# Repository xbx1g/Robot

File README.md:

# 🤖 Robotic Arm with Mecanum Wheels

This project is a **final thesis** for the vocational matura exam.  
It is a mobile robot with **mecanum wheels** and a **robotic arm**, controllable via **Bluetooth** using a custom mobile app.  
The project combines **mechanical engineering, electronics, and programming** – from CAD design and 3D printing, to PCB design, Arduino programming, and mobile app development.

---

## 📌 Features

- Omni-directional movement with **mecanum wheels**  
- **Robotic arm** with multiple degrees of freedom (servo motors)  
- Custom-designed **PCB** for component management  
- **Arduino Mega 2560** as the main controller  
- Control via **Bluetooth module HC-05** and a mobile app (MIT App Inventor)  
- **3D-printed parts** made from PETG filament  
- Powered and tested with **11.1V 3300 mAh LiPo battery**  

---

## 🛠️ Components Used

- Arduino Mega 2560  
- Servo motors (MG996R, SG90)  
- Bipolar stepper motors + **DRV8825 drivers**  
- Bluetooth module **HC-05**  
- Voltage regulator **LM2596**  
- Custom-designed **PCB** (Eagle CAD)  
- 3D-printed parts (Autodesk Inventor + PrusaSlicer, Ender 3 S1 printer)  

---

## 📱 Mobile App

Developed with **MIT App Inventor**.  
Main features:  
- Control of chassis movement (forward/backward/left/right/diagonal)  
- Control of robotic arm (individual joints)  
- Save and execute movement sequences  
- Adjust motor speeds  

---

## 💻 Arduino Code

The Arduino firmware is organized into several modules:  
- **Main program** (initialization, Bluetooth connection)  
- **Chassis movement control**  
- **Robotic arm control**  
- **Movement sequence storage and execution**  
- **Battery voltage monitoring** with LED warning  

---

## 🚀 Getting Started

1. Assemble the robot (chassis, arm, PCB, and wiring).  
2. Upload the Arduino code to **Arduino Mega 2560**.  
3. Install the mobile app (APK) on your smartphone.  
4. Pair with the **HC-05 Bluetooth module**.  
5. Start controlling the robot and test the functionalities.  

---

## 📊 Testing Results

- Battery runtime: ~30 minutes  
- Stepper motor driver temperature after 30 minutes: **45–55 °C**  
- Robot successfully performs omni-directional movements and basic manipulation tasks  

---

## 🔮 Future Improvements

- Add **LCD display** for battery monitoring and step sequence display  
- Support for **Xbox / other Bluetooth controllers**  
- Further PCB optimization and cable management  

---

## 👤 Author

**Marko Koren**  
Mentor: **Peter Zoroja**  
Šolski center Nova Gorica, 2024

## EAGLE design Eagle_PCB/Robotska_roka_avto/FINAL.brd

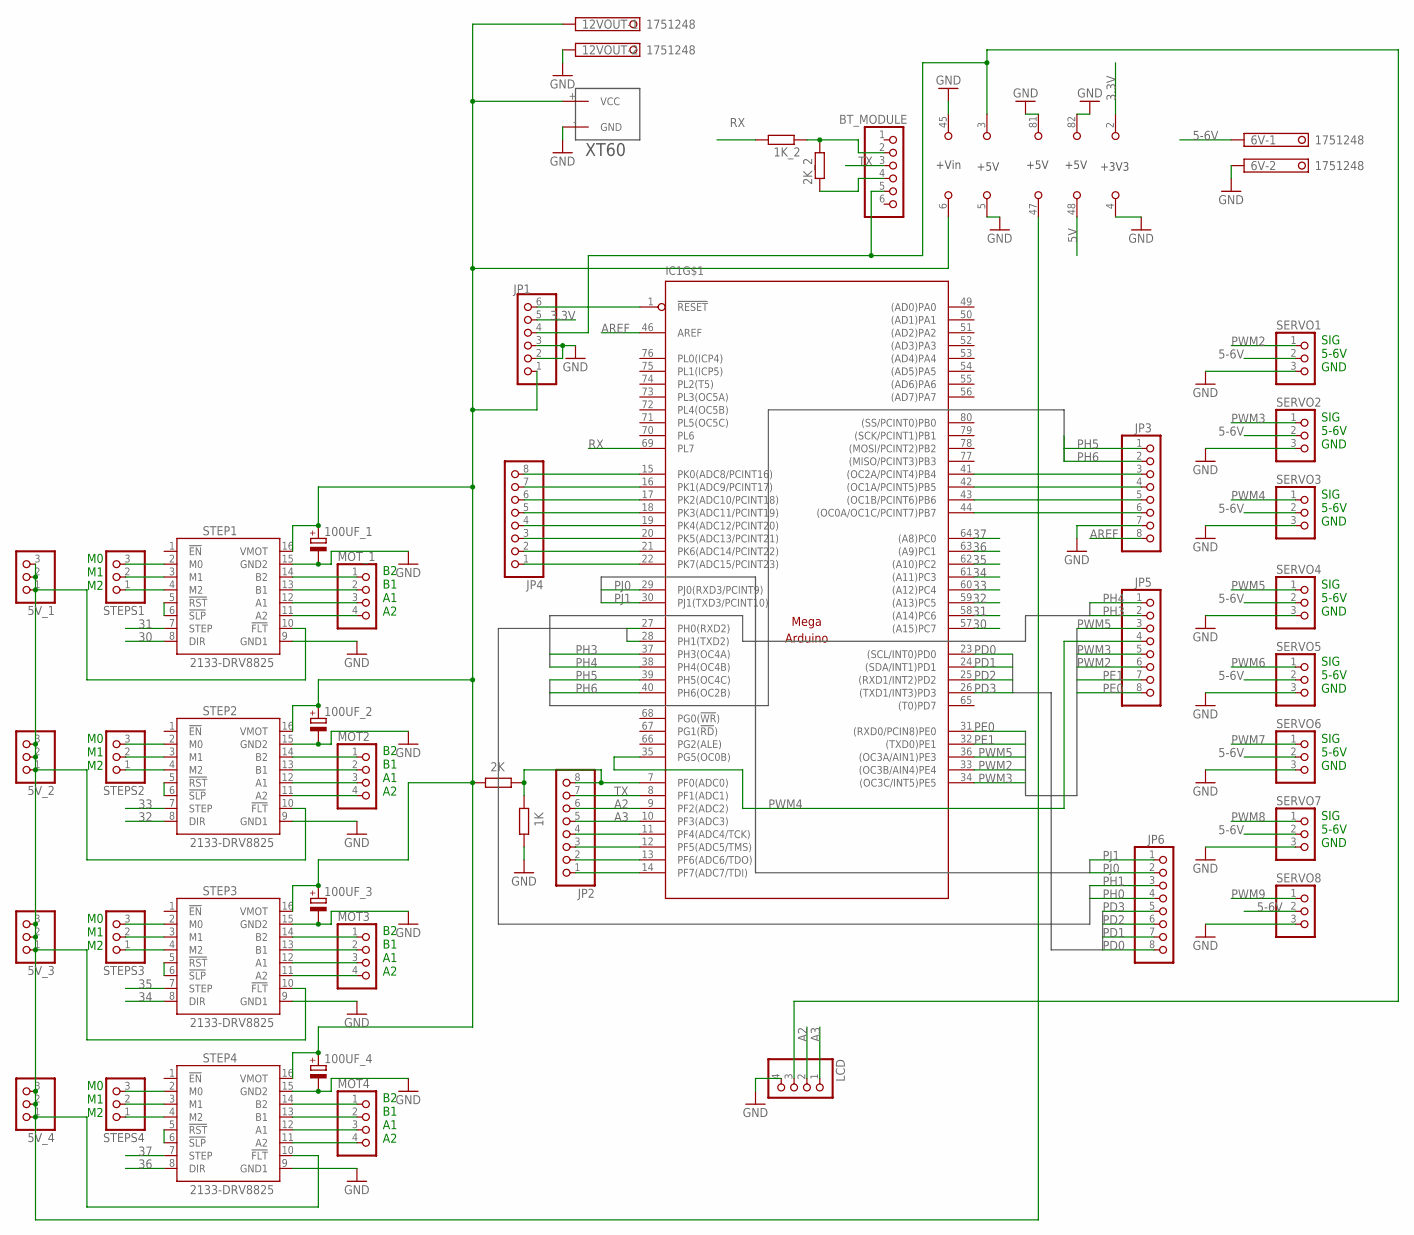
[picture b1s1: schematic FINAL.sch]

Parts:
1K, 1K_2, 2K, 2K_2: R-EU_0204/7; 0204/7
5V_1, 5V_2, 5V_3, 5V_4: PINHD-1X3; 1X03
6V, 12VOUT: 1751248
100UF_1, 100UF_2, 100UF_3, 100UF_4: CPOL-EUE5-5; E5-5
BT_MODULE: PINHD-1X6; 1X06
IC1: MEGAARDUINO_22; MEGA_ARDUINO_2
JP1: PINHD-1X6; 1X06
JP2, JP3, JP4, JP5, JP6: PINHD-1X8; 1X08
LCD: PINHD-1X4; 1X04
MOT2, MOT3, MOT4: PINHD-1X4; 1X04
MOT_1: PINHD-1X4; 1X04
SERVO1, SERVO2, SERVO3, SERVO4, SERVO5, SERVO6, SERVO7, SERVO8: PINHD-1X3; 1X03
STEP1, STEP2, STEP3, STEP4: 2133-DRV8825; DRV8825
STEPS1, STEPS2, STEPS3, STEPS4: PINHD-1X3; 1X03
U$1: XT60

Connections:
3.3V: IC1.2 (+3V3), JP1.5
5-6V: 6V.1, SERVO1.2, SERVO2.2, SERVO3.2, SERVO4.2, SERVO5.2, SERVO6.2, SERVO7.2, SERVO8.2
5V: IC1.48 (+5V)
12V1: 2K.1, 12VOUT.1, 100UF_1.+, 100UF_2.+, 100UF_3.+, 100UF_4.+, IC1.6 (+VIN), JP1.1, STEP1.16 (VMOT), STEP2.16 (VMOT), STEP3.16 (VMOT), STEP4.16 (VMOT), U$1.+ (VCC)
30: IC1.57 ((A15)PC7), STEP1.8 (DIR)
31: IC1.58 ((A14)PC6), STEP1.7 (STEP)
32: IC1.59 ((A13)PC5), STEP2.8 (DIR)
33: IC1.60 ((A12)PC4), STEP2.7 (STEP)
34: IC1.61 ((A11)PC3), STEP3.8 (DIR)
35: IC1.62 ((A10)PC2), STEP3.7 (STEP)
36: IC1.63 ((A9)PC1), STEP4.8 (DIR)
37: IC1.64 ((A8)PC0), STEP4.7 (STEP)
A2: IC1.9 (PF2(ADC2)), JP2.6, LCD.2
A3: IC1.10 (PF3(ADC3)), JP2.5, LCD.1
AREF: IC1.46 (AREF), JP3.8
GND: 1K.2, 6V.2, 12VOUT.2, 100UF_1.-, 100UF_2.-, 100UF_3.-, 100UF_4.-, IC1.4 (GND), IC1.5 (GND), IC1.45 (GND), IC1.81 (GND), IC1.82 (GND), JP1.2, JP1.3, JP3.7, LCD.4, SERVO1.3, SERVO2.3, SERVO3.3, SERVO4.3, SERVO5.3, SERVO6.3, SERVO7.3, SERVO8.3, STEP1.9 (GND1), STEP1.15 (GND2), STEP2.9 (GND1), STEP2.15 (GND2), STEP3.9 (GND1), STEP3.15 (GND2), STEP4.9 (GND1), STEP4.15 (GND2), U$1.- (GND)
unnamed: IC1.11 (PF4(ADC4/TCK)), JP2.4
unnamed: MOT_1.1, STEP1.14 (B2)
unnamed: MOT_1.2, STEP1.13 (B1)
unnamed: MOT_1.3, STEP1.12 (A1)
unnamed: MOT_1.4, STEP1.11 (A2)
unnamed: MOT2.1, STEP2.14 (B2)
unnamed: MOT2.2, STEP2.13 (B1)
unnamed: MOT2.3, STEP2.12 (A1)
unnamed: MOT2.4, STEP2.11 (A2)
unnamed: MOT3.1, STEP3.14 (B2)
unnamed: MOT3.2, STEP3.13 (B1)
unnamed: MOT3.3, STEP3.12 (A1)
unnamed: MOT3.4, STEP3.11 (A2)
unnamed: MOT4.1, STEP4.14 (B2)
unnamed: MOT4.2, STEP4.13 (B1)
unnamed: MOT4.3, STEP4.12 (A1)
unnamed: MOT4.4, STEP4.11 (A2)
unnamed: STEP1.2 (M0), STEPS1.3
unnamed: 2K_2.1, BT_MODULE.4
unnamed: 1K_2.1, 2K_2.2, BT_MODULE.2
unnamed: STEP1.3 (M1), STEPS1.2
unnamed: STEP1.4 (M2), STEPS1.1
unnamed: STEP2.2 (M0), STEPS2.3
unnamed: STEP2.3 (M1), STEPS2.2
unnamed: STEP2.4 (M2), STEPS2.1
unnamed: STEP3.2 (M0), STEPS3.3
unnamed: STEP3.3 (M1), STEPS3.2
unnamed: STEP3.4 (M2), STEPS3.1
unnamed: STEP4.2 (M0), STEPS4.3
unnamed: STEP4.3 (M1), STEPS4.2
unnamed: STEP4.4 (M2), STEPS4.1
unnamed: STEP1.5 (!RST), STEP1.6 (!SLP)
unnamed: STEP2.5 (!RST), STEP2.6 (!SLP)
unnamed: STEP3.5 (!RST), STEP3.6 (!SLP)
unnamed: STEP4.5 (!RST), STEP4.6 (!SLP)
unnamed: 5V_1.1, 5V_1.2, 5V_1.3, 5V_2.1, 5V_2.2, 5V_2.3, 5V_3.1, 5V_3.2, 5V_3.3, 5V_4.1, 5V_4.2, 5V_4.3, IC1.47 (+5V), STEP1.10 (!FLT), STEP2.10 (!FLT), STEP3.10 (!FLT), STEP4.10 (!FLT)
unnamed: IC1.1 (!RESET), JP1.6
unnamed: 1K.1, 2K.2, IC1.7 (PF0(ADC0)), JP2.8
unnamed: IC1.12 (PF5(ADC5/TMS)), JP2.3
unnamed: IC1.13 (PF6(ADC6/TDO)), JP2.2
unnamed: IC1.14 (PF7(ADC7/TDI)), JP2.1
unnamed: IC1.15 (PK0(ADC8/PCINT16)), JP4.8
unnamed: IC1.16 (PK1(ADC9/PCINT17)), JP4.7
unnamed: IC1.17 (PK2(ADC10/PCINT18)), JP4.6
unnamed: IC1.18 (PK3(ADC11/PCINT19)), JP4.5
unnamed: IC1.19 (PK4(ADC12/PCINT20)), JP4.4
unnamed: IC1.20 (PK5(ADC13/PCINT21)), JP4.3
unnamed: IC1.21 (PK6(ADC14/PCINT22)), JP4.2
unnamed: IC1.22 (PK7(ADC15/PCINT23)), JP4.1
unnamed: IC1.44 ((OC0A/OC1C/PCINT7)PB7), JP3.6
unnamed: IC1.43 ((OC1B/PCINT6)PB6), JP3.5
unnamed: IC1.42 ((OC1A/PCINT5)PB5), JP3.4
unnamed: IC1.41 ((OC2A/PCINT4)PB4), JP3.3
unnamed: BT_MODULE.5, IC1.3 (+5V), JP1.4, LCD.3
PD0: IC1.23 ((SCL/INT0)PD0), JP6.8
PD1: IC1.24 ((SDA/INT1)PD1), JP6.7
PD2: IC1.25 ((RXD1/INT2)PD2), JP6.6
PD3: IC1.26 ((TXD1/INT3)PD3), JP6.5
PE0: IC1.31 ((RXD0/PCIN8)PE0), JP5.8
PE1: IC1.32 ((TXD0)PE1), JP5.7
PH0: IC1.27 (PH0(RXD2)), JP6.4
PH1: IC1.28 (PH1(TXD2)), JP6.3
PH3: IC1.37 (PH3(OC4A)), JP5.2
PH4: IC1.38 (PH4(OC4B)), JP5.1
PH5: IC1.39 (PH5(OC4C)), JP3.1
PH6: IC1.40 (PH6(OC2B)), JP3.2
PJ0: IC1.29 (PJ0(RXD3/PCINT9)), JP6.2
PJ1: IC1.30 (PJ1(TXD3/PCINT10)), JP6.1
PWM2: IC1.33 ((OC3B/AIN4)PE4), JP5.6, SERVO1.1
PWM3: IC1.34 ((OC3C/INT5)PE5), JP5.5, SERVO2.1
PWM4: IC1.35 (PG5(OC0B)), JP5.4, SERVO3.1
PWM5: IC1.36 ((OC3A/AIN1)PE3), JP5.3, SERVO4.1
PWM6: SERVO5.1
PWM7: SERVO6.1
PWM8: SERVO7.1
PWM9: SERVO8.1
RX: 1K_2.2, IC1.69 (PL7)
TX: BT_MODULE.3, IC1.8 (PF1(ADC1)), JP2.7

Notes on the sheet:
B2 B1 A1 A2
M0 M1 M2
SIG 5-6V GND

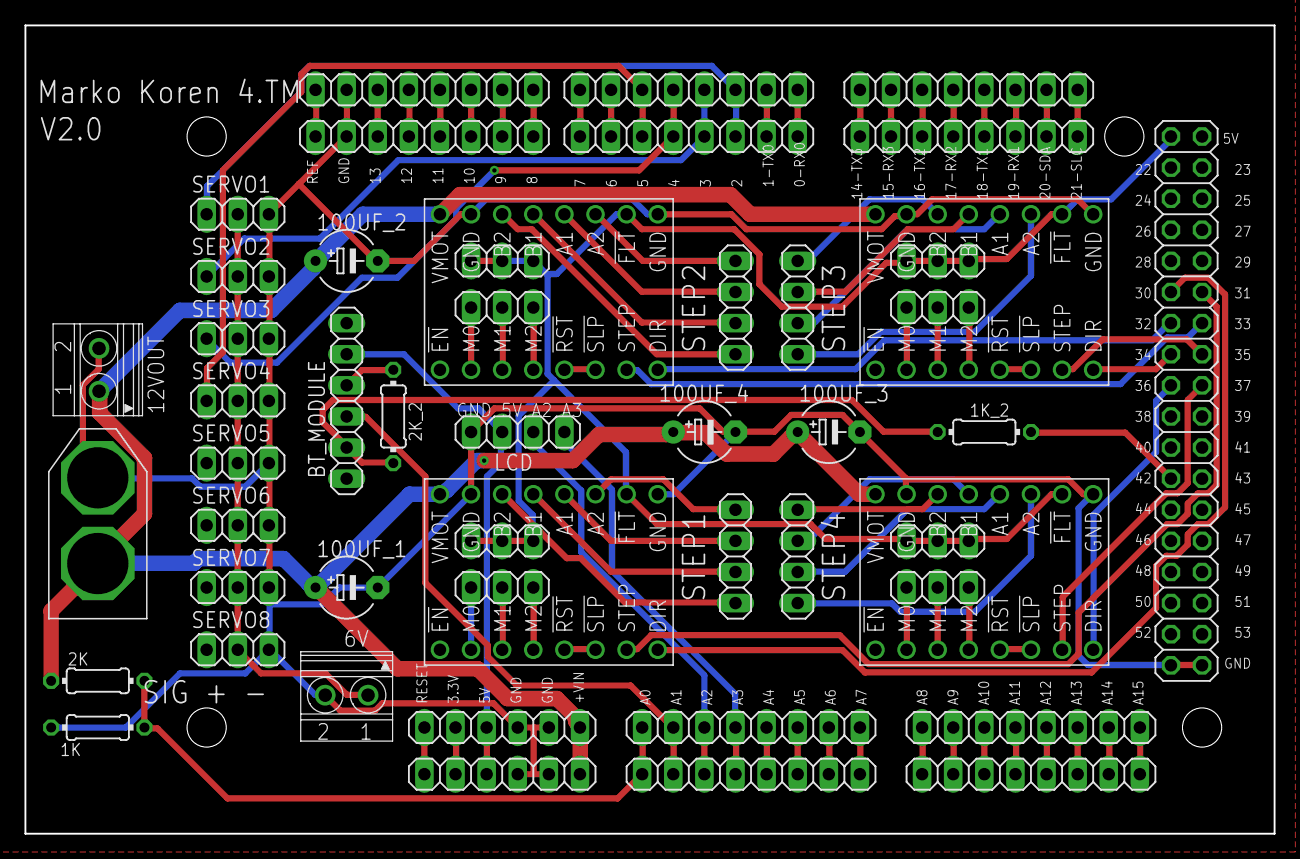
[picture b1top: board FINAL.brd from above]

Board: 2 copper layers, 102.0 x 66.0 mm, 44 parts (0 on the bottom side), 89 nets.

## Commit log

2025-09-28 ADDING EVERYTHIG
    ADDING EVERYTHING I DID FOR THE PROJECT
2025-09-28 README.md
